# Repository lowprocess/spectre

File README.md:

# spectre

- [sim/](sim/README.md): a simulation of the signal chain (noise, images,
  spurs, distortion, the ADC), with its report in
  [sim/results/proposal/report.md](sim/results/proposal/report.md).
- [docs/schematic.md](docs/schematic.md): the 6.4 GHz proposal as a KiCad
  schematic ([PDF](docs/schematic.pdf)) and a board floorplan with the
  printed filters ([image](docs/floorplan.svg)); what is still open before
  layout.

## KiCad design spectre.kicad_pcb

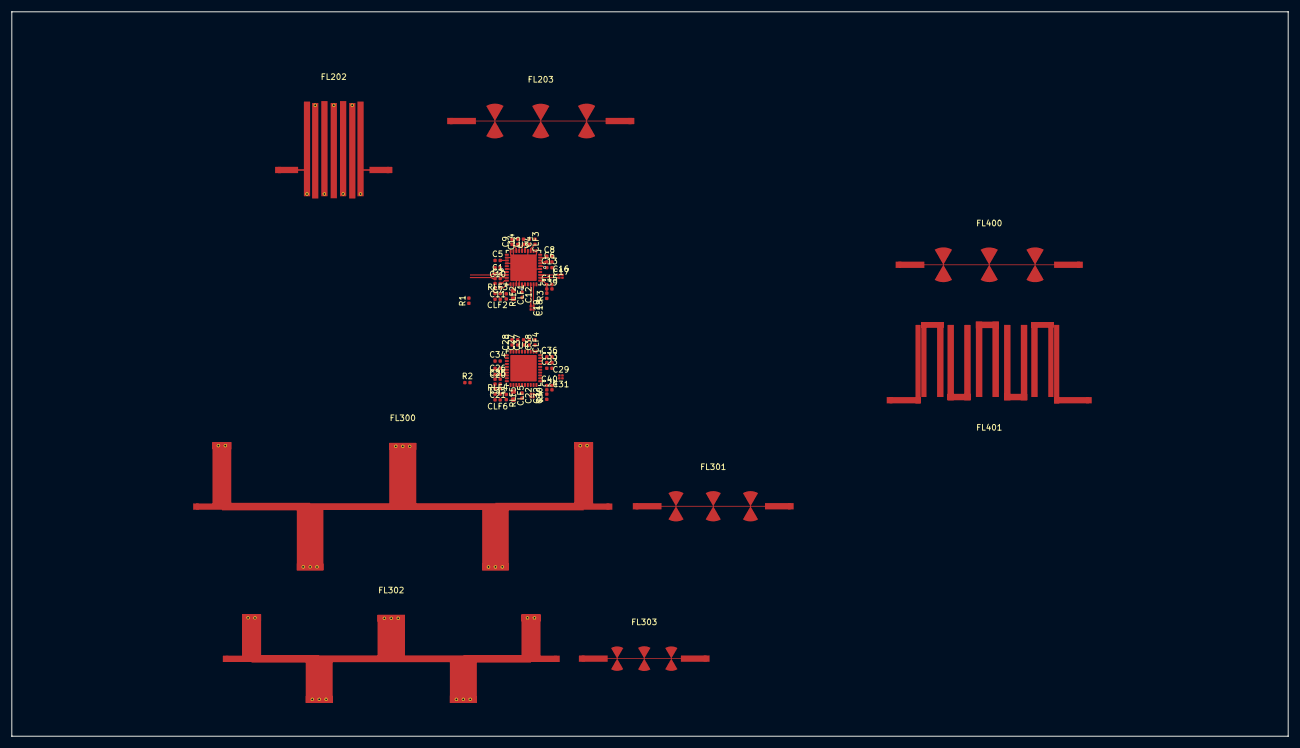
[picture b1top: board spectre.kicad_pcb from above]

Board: 4 copper layers, 222.0 x 126.0 mm, 64 parts (0 on the bottom side), 39 nets.

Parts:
C1, C2, C6, C10, C11, C15, C20, C21, C24, C25, C26, C33: 100nF; C_0402
C3, C4, C8, C36, C37, C38: 10uF; C_0402
C5, C34: 470nF; C_0402
C7, C12, C13, C14, C22, C23, C27, C35, C39, C40: 1uF; C_0402
C9, C28: 10nF; C_0402
C16, C17, C18, C19, C29, C30, C31, C32: 22pF; C_0201
CLF1, CLF5: 0pF; C_0603
CLF2, CLF3, CLF4, CLF6: 0pF; C_0402
FL202: BPF 2.3-3.0 GHz; l2_bpf_2g3_3g0_interdigital
FL203, FL400: LPF 4.0 GHz; if1_lpf_4g0_radial
FL300: BPF 2.9-4.5 GHz; h1_bpf_3g0_4g5_stub
FL301: LPF 5.0 GHz; h1_lpf_5g0_radial
FL302: BPF 4.3-6.4 GHz; h2_bpf_4g3_6g4_stub
FL303: LPF 7.0 GHz; h2_lpf_7g0_radial
FL401: BPF 3.4 GHz; if1_bpf_3g4_hairpin
R1, R2, R3, R4: 0R; R_0402
RLF2, RLF3, RLF4, RLF5: TBD; R_0402
U3, U4: QFN40

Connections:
/LO1/3V3_BUF: C15.1, C39.1, R3.2, U3.21 (VccBUF)
/LO1/3V3_SYN: C10.1, C11.1, C12.1, C13.1, C14.1, R1.2, U3.7 (VccDIG), U3.11 (VccCP), U3.15 (VccMASH), U3.26 (VccVCO2), U3.37 (VccVCO)
/LO1/CPOut: CLF1.1, RLF2.1, RLF3.2, U3.12 (CPout)
/LO1/OSC_N: C2.2, U3.9 (OSCinM)
/LO1/OSC_P: C1.2, U3.8 (OSCinP)
/LO1/RF_A_N: C17.1, U3.22 (RFoutAM)
/LO1/RF_A_P: C16.1, U3.23 (RFoutAP)
/LO1/RF_B_N: C19.1, U3.18 (RFoutBM)
/LO1/RF_B_P: C18.1, U3.19 (RFoutBP)
/LO1/VTUNE: CLF3.2, RLF3.1, U3.35 (Vtune)
/LO1/VbiasVARAC: C4.1, U3.33 (VbiasVARAC)
/LO1/VbiasVCO: C5.2, U3.3 (VbiasVCO)
/LO1/VbiasVCO2: C6.1, U3.27 (VbiasVCO2)
/LO1/VrefVCO: C3.1, U3.36 (VrefVCO)
/LO1/VrefVCO2: C8.1, U3.29 (VrefVCO2)
/LO1/VregIN: C7.1, U3.10 (VregIN)
/LO1/VregVCO: C9.1, U3.38 (VregVCO)
/LO2/3V3_BUF: C24.1, C40.1, R4.2, U4.21 (VccBUF)
/LO2/3V3_SYN: C20.1, C21.1, C22.1, C23.1, C27.1, R2.2, U4.7 (VccDIG), U4.11 (VccCP), U4.15 (VccMASH), U4.26 (VccVCO2), U4.37 (VccVCO)
/LO2/CPOut: CLF5.1, RLF4.2, RLF5.1, U4.12 (CPout)
/LO2/OSC_N: C25.2, U4.9 (OSCinM)
/LO2/OSC_P: C26.2, U4.8 (OSCinP)
/LO2/RF_A_N: C31.1, U4.22 (RFoutAM)
/LO2/RF_A_P: C29.1, U4.23 (RFoutAP)
/LO2/RF_B_N: C32.1, U4.18 (RFoutBM)
/LO2/RF_B_P: C30.1, U4.19 (RFoutBP)
/LO2/VTUNE: CLF4.2, RLF4.1, U4.35 (Vtune)
/LO2/VbiasVARAC: C38.1, U4.33 (VbiasVARAC)
/LO2/VbiasVCO: C34.2, U4.3 (VbiasVCO)
/LO2/VbiasVCO2: C33.1, U4.27 (VbiasVCO2)
/LO2/VrefVCO: C37.1, U4.36 (VrefVCO)
/LO2/VrefVCO2: C36.1, U4.29 (VrefVCO2)
/LO2/VregIN: C35.1, U4.10 (VregIN)
/LO2/VregVCO: C28.1, U4.38 (VregVCO)
GND: C3.2, C4.2, C5.1, C6.2, C7.2, C8.2, C9.2, C10.2, C11.2, C12.2, C13.2, C14.2, C15.2, C20.2, C21.2, C22.2, C23.2, C24.2, C27.2, C28.2, C33.2, C34.1, C35.2, C36.2, C37.2, C38.2, C39.2, C40.2, CLF1.2, CLF2.2, CLF3.1, CLF4.1, CLF5.2, CLF6.2, U3.2 (GND), U3.4 (GND), U3.6 (GND), U3.13 (GND), U3.14 (GND), U3.25 (GND), U3.31 (GND), U3.34 (GND), U3.39 (GND), U3.40 (GND), U3.EP (GND), U4.2 (GND), U4.4 (GND), U4.6 (GND), U4.13 (GND), U4.14 (GND), U4.25 (GND), U4.31 (GND), U4.34 (GND), U4.39 (GND), U4.40 (GND), U4.EP (GND)
G_3V3_BUF: R3.1, R4.1
G_3V3_SYN: R1.1, R2.1
unnamed: CLF2.1, RLF2.2
unnamed: CLF6.1, RLF5.2
